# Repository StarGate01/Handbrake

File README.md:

# Handbrake

Firmware and Hardware for an analog handbrake game controller using an attiny85 and V-USB: https://www.obdev.at/products/vusb/index.html

Based on the EasyLogger project: https://www.obdev.at/products/vusb/easylogger.html

Hardware designed wich KiCAD

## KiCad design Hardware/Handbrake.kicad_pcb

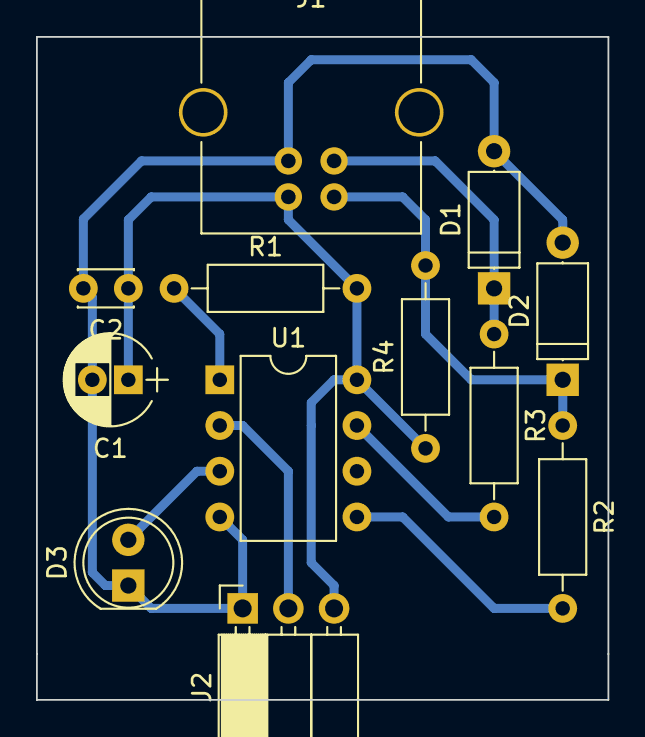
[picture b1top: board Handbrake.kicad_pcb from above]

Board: 2 copper layers, 31.8 x 36.8 mm, 12 parts (0 on the bottom side), 9 nets.

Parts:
C1: 10u; CP_Radial_D5.0mm_P2.00mm
C2: 0.1u; C_Disc_D3.0mm_W2.0mm_P2.50mm
D1, D2: 3.6; D_A-405_P7.62mm_Horizontal
D3: Red; LED_D5.0mm
J1: USB_B
J2: Sensor_Female; Socket_Strip_Angled_1x03_Pitch2.54mm
R1: 4.7K; R_Axial_DIN0207_L6.3mm_D2.5mm_P10.16mm_Horizontal
R2, R3: 68; R_Axial_DIN0207_L6.3mm_D2.5mm_P10.16mm_Horizontal
R4: 2.2K; R_Axial_DIN0207_L6.3mm_D2.5mm_P10.16mm_Horizontal
U1: ATTINY85-20PU; DIP-8_W7.62mm

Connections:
unnamed: C1.1, C2.1, J1.1, J2.3, R1.2, R4.1, U1.8
unnamed: C1.2, C2.2, D1.2, D2.2, D3.1, J1.4, J2.1, U1.4
unnamed: D1.1, J1.3, R3.1
unnamed: D2.1, J1.2, R2.1, R4.2
unnamed: D3.2, U1.3
unnamed: J2.2, U1.2
unnamed: R1.1, U1.1
unnamed: R2.2, U1.5
unnamed: R3.2, U1.7

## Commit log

2017-11-04 Added easylogger files
2017-11-04 Fix include paths
2017-11-05 Refractor and Adjust Aref
2017-11-05 working hid joystick descriptor
2017-11-05 First working version
2017-11-09 Add Hardware files
2017-11-09 Move files
2017-11-13 add status led
